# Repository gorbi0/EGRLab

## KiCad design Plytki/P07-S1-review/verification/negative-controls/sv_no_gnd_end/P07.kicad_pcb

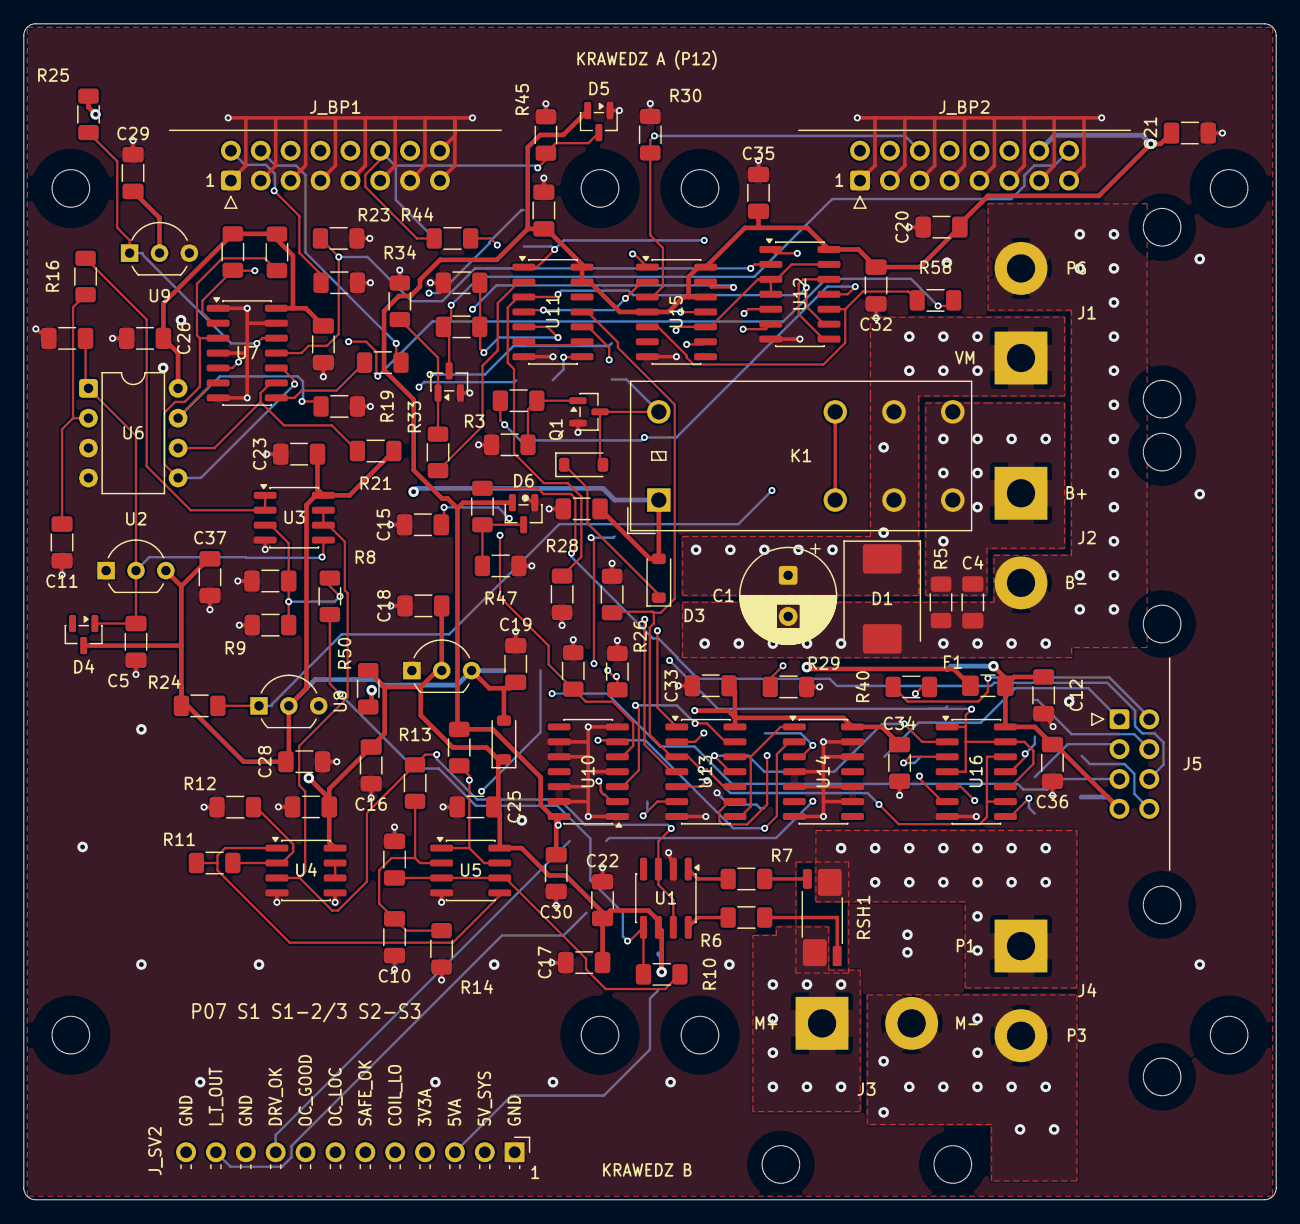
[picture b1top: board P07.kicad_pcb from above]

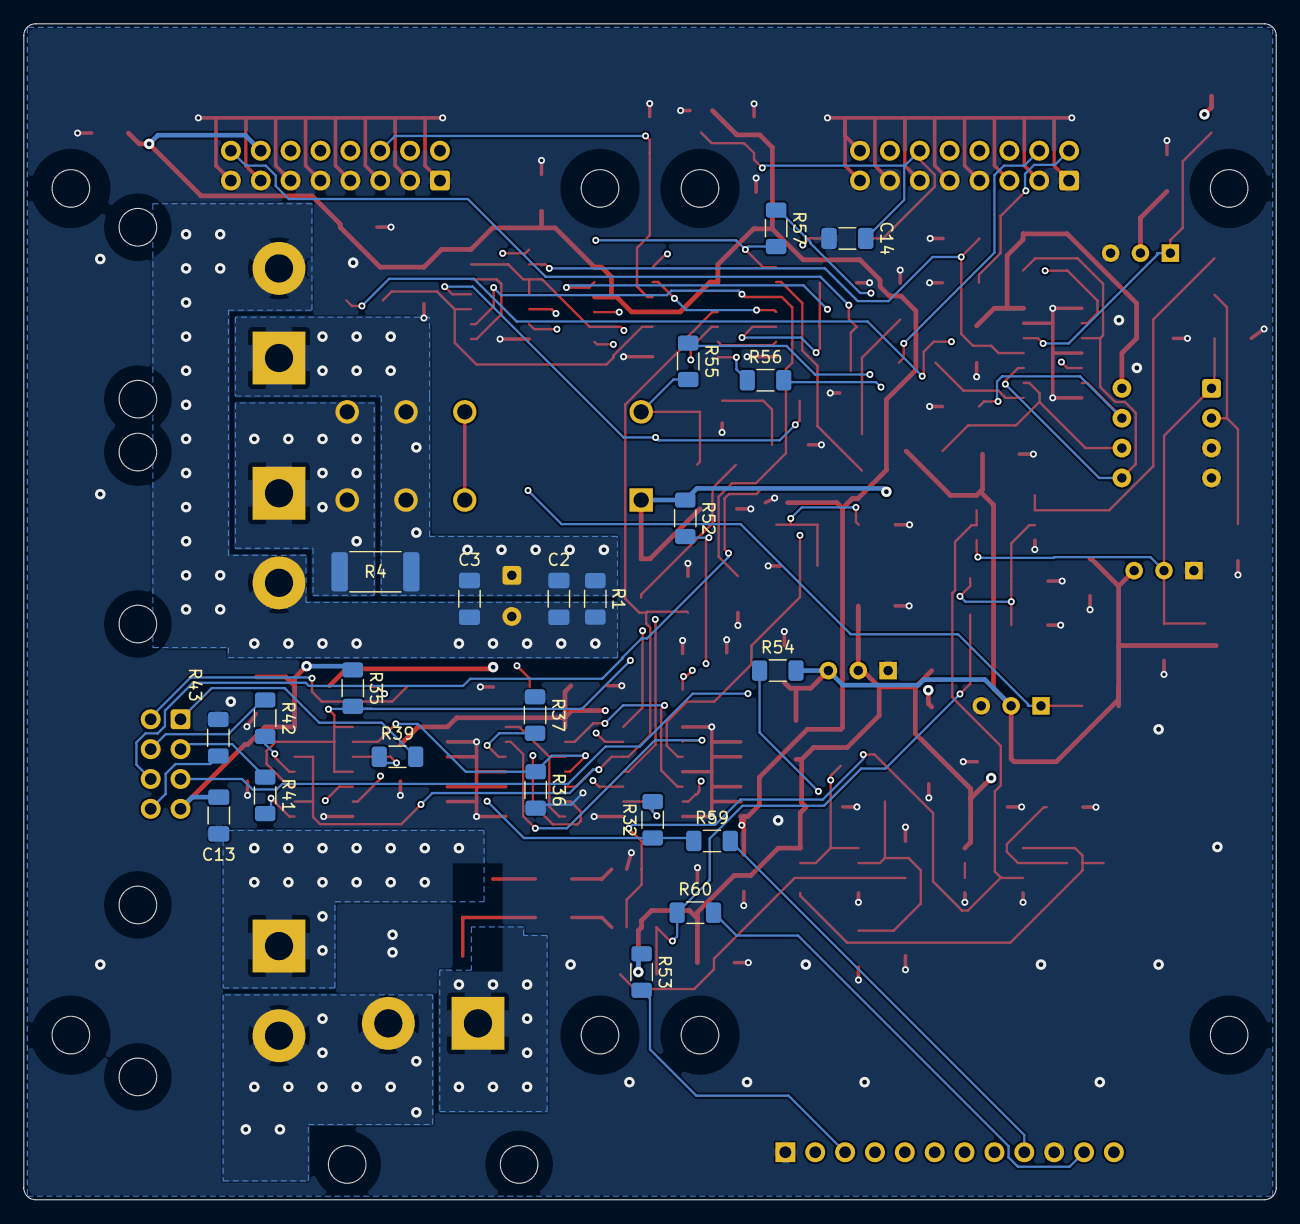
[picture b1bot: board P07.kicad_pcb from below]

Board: 4 copper layers, 106.5 x 100.0 mm, 140 parts (22 on the bottom side), 90 nets.

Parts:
C1: 220u; CP_Radial_D8.0mm_P3.50mm
C2, C18: 1u; C_1206_3216Metric_Pad1.33x1.80mm_HandSolder
C3, C4, C6, C7, C13, C14, C15, C17, C20, C22, C23, C24, C25, C26, C27, C28, C29, C30, C31, C32, C33, C34, C35, C36, C37: 100n; C_1206_3216Metric_Pad1.33x1.80mm_HandSolder
C5, C19: 4.7u; C_1206_3216Metric_Pad1.33x1.80mm_HandSolder
C8: 1n; C_1206_3216Metric_Pad1.33x1.80mm_HandSolder
C9, C12, C16, C21: 10u; C_1206_3216Metric_Pad1.33x1.80mm_HandSolder
C10: 10n; C_1206_3216Metric_Pad1.33x1.80mm_HandSolder
C11: 470p; C_1206_3216Metric_Pad1.33x1.80mm_HandSolder
D1: SMCJ18A; D_SMC
D2: 1N4148W; D_SOD-123
D3: BZT52C15; D_SOD-123
D4: BAT54; SOT-23
D5, D6: BAT54S; SOT-23
D7: B5819W; D_SOD-123
F1: PTC 0.12A; Fuse_1206_3216Metric_Pad1.42x1.75mm_HandSolder
H1, H2, H3, H4, H5, H6, H7, H8: M3 NPTH
J1: VMOTOR; PTH_VMOTOR
J2: MOD B+/B-; PTH_MODPWR
J3: MOD M+/M-; PTH_MODOUT
J4: TEST; PTH_TEST
J5: J_MOD; IDC-Header_2x04_P2.54mm_Horizontal
J_BP1: J_BP1; IDC-Header_2x08_P2.54mm_Horizontal
J_BP2: J_BP2; IDC-Header_2x08_P2.54mm_Horizontal
J_SV2: J_SV2 SERWIS 1x12; PinHeader_1x12_P2.54mm_Horizontal
K1: G2RL-1-E DC5; Relay_SPDT_Omron_G2RL-1-E
Q1: AO3400A; SOT-23
Q2: MMBT3904; SOT-23
R1, R5, R12, R14, R15, R18, R19, R23, R24, R25, R33, R60: 10K; R_1206_3216Metric_Pad1.30x1.75mm_HandSolder
R2, R32, R39, R40, R41, R42: 100R; R_1206_3216Metric_Pad1.30x1.75mm_HandSolder
R3, R17, R20, R26, R27, R28, R29, R30, R34, R35, R36, R37, R38, R45, R47: 100K; R_1206_3216Metric_Pad1.30x1.75mm_HandSolder
R4: 1K; R_2512_6332Metric_Pad1.40x3.35mm_HandSolder
R6, R7, R43, R50: 10R; R_1206_3216Metric_Pad1.30x1.75mm_HandSolder
R8, R9: 5.11K; R_1206_3216Metric_Pad1.30x1.75mm_HandSolder
R10, R31, R52, R53, R54, R55, R56, R57, R58, R59: 1K; R_1206_3216Metric_Pad1.30x1.75mm_HandSolder
R11: 8.06K; R_1206_3216Metric_Pad1.30x1.75mm_HandSolder
R13: 40.2K; R_1206_3216Metric_Pad1.30x1.75mm_HandSolder
R16, R22: 47R; R_1206_3216Metric_Pad1.30x1.75mm_HandSolder
R21: 47K; R_1206_3216Metric_Pad1.30x1.75mm_HandSolder
R44, R46: 4K7; R_1206_3216Metric_Pad1.30x1.75mm_HandSolder
R51: 1M; R_1206_3216Metric_Pad1.30x1.75mm_HandSolder
RSH1: 5m; R_Shunt_Vishay_WSK2512_T1.19mm_SenseE1.70
U1: INA240A2; SOIC-8_3.9x4.9mm_P1.27mm
U2: MCP1525-I/TO; TO-92_Inline_Wide
U3, U4: MCP6022-I/SN; SOIC-8_3.9x4.9mm_P1.27mm
U5: TLV1702AIDR; SOIC-8_3.9x4.9mm_P1.27mm
U6: MCP3201-BI/P; DIP-8_W7.62mm
U7, U10: 74LVC125AD; SOIC-14_3.9x8.7mm_P1.27mm
U8: MCP120-300DI/TO; TO-92_Inline_Wide
U9: MCP120-450DI/TO; TO-92_Inline_Wide
U11: 74LVC14AD; SOIC-14_3.9x8.7mm_P1.27mm
U12, U13, U14: SN74HC08D; SOIC-14_3.9x8.7mm_P1.27mm
U15: SN74HC74D; SOIC-14_3.9x8.7mm_P1.27mm
U16: 74AHCT125D; SOIC-14_3.9x8.7mm_P1.27mm
U18: MCP1702-3302E/TO; TO-92_Inline_Wide

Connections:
3V3A_P07: C19.1, C23.1, C26.1, C27.1, C28.1, C37.1, D4.3, D7.2, R17.1, R18.1, R21.1, R24.1, R54.1, U2.3, U3.8, U6.8, U7.14, U8.2, U18.3
3V3_IO: C20.1, C21.1, C30.1, C31.1, C32.1, C33.1, C34.1, C35.1, D5.2, D6.2, J_BP2.14, R15.2, U10.14, U11.13, U11.14, U12.14, U13.14, U14.14, U15.4, U15.12, U15.14
5VA_P07: C16.1, C17.1, C18.1, C22.1, C24.1, C25.1, C29.1, D7.1, R25.1, R50.2, R53.1, U1.6, U4.8, U5.8, U9.2, U18.2
5V_MOD: C12.1, C13.1, C36.1, F1.2, J5.7, R35.1, U16.14
5V_SYS: C9.1, D3.2, F1.1, J_BP2.10, J_BP2.12, K1.A1, R50.1, R52.1
/ANA/INA_MINUS: R7.2, U1.1
/ANA/INA_PLUS: R6.2, U1.8
/ANA/I_DIV: C7.1, R8.2, R9.1, U3.3
/ANA/I_FILT: C8.1, R10.2, U5.3, U5.6
/ANA/OC_FB: R11.2, R12.1, U4.2
/ANA/OC_HIGH: R11.1, U4.1, U5.5
/ANA/OC_LOW: C10.1, R13.2, R14.1, U5.2
/ANA/OC_UNUSED: U4.6, U4.7
/ANA/REF_BUF: R13.1, U1.3, U1.7, U3.6, U3.7, U4.3
/DIG/ADC_AIN: C11.1, R16.2, U6.2
/DIG/ADC_DOUT: R21.2, U6.6, U7.9
/DIG/CLK_LOCAL: R19.1, U6.7, U7.6
/DIG/CS_LOCAL_N: R18.2, U6.5, U7.3, U7.10
/DIG/DOUT_TX: R22.1, U7.8
/LOGIKA/DRIVE_OK_L: R32.1, U13.6
/LOGIKA/INA_P07: U10.3, U13.13
/LOGIKA/INB_P07: U10.6, U14.2
/LOGIKA/LOCAL_CLEAR_N: U12.6, U15.1
/LOGIKA/NO_TRIP: U13.5, U15.9
/LOGIKA/OC_B: Q2.1, R33.2, R34.1
/LOGIKA/OC_FAULT: R33.1, U11.2
/LOGIKA/PERMIT_ARMED: U12.8, U12.12
/LOGIKA/PERMIT_N: U11.4, U15.2
/LOGIKA/PWM_EN: U13.8, U13.12, U14.1
/LOGIKA/RAILS_OK: U12.3, U12.4, U12.13, U13.4, U15.10
/LOGIKA/SAFE_BAD: U11.6, U11.9
/LOGIKA/SAFE_SENSE: R31.2, R51.1, U11.5
/LOGIKA/SUP3_N: R24.2, U8.1, U12.1
/MOC/KPWR_B: Q1.1, R2.2, R3.1
/MOC/KPWR_CLAMP: D2.1, D3.1
/MOC/MOD_BP: C4.1, J2.1, K1.14, R4.2, R5.1
/MOC/MOD_MP: J3.1, RSH1.1
/MOC/T_EGR_P1: J4.1, RSH1.4
/MOC/T_EGR_P3: J3.2, J4.2
/MODUL/LEN_D: R42.1, U16.11
/MODUL/LPWM: J5.2, R40.2
/MODUL/LPWM_D: R40.1, U16.6
/MODUL/L_EN: J5.4, R42.2
/MODUL/L_IS: J5.6, R46.1
/MODUL/MOD_GND: J5.8, R43.2
/MODUL/REN_D: R41.1, U16.8
/MODUL/RPWM: J5.1, R39.2
/MODUL/RPWM_D: R39.1, U16.3
/MODUL/R_EN: J5.3, R41.2
/MODUL/R_IS: J5.5, R44.1
/SERWIS/SRV_3V3A_P07: J_SV2.4, R54.2
/SERWIS/SRV_5VA_P07: J_SV2.3, R53.2
/SERWIS/SRV_5V_SYS: J_SV2.2, R52.2
/SERWIS/SRV_DRIVE_OK: J_SV2.9, R59.2
/SERWIS/SRV_I_T_OUT: J_SV2.11, J_SV2.12, R60.2
/SERWIS/SRV_KPWR_COIL_LOW: J_SV2.5, R55.2
/SERWIS/SRV_OC_GOOD: J_SV2.8, R58.2
/SERWIS/SRV_OC_LOCAL_N: J_SV2.7, R57.2
/SERWIS/SRV_SAFE_OK: J_SV2.6, R56.2
ADC_BUF: R16.1, U3.1, U3.2
ADC_DOUTA: J_BP1.4, R22.2
ADC_SCLK: J_BP1.2, R20.1, U7.5
ARM_CLK: J_BP2.6, R30.1, U15.3, U15.11
CS_ITEST_N: J_BP1.6, R17.2, U7.2
DRIVE_EN: R38.1, U11.11, U13.3, U13.10, U16.9, U16.12
DRIVE_OK: J_BP2.8, R32.2, R59.1
DRV_OFF: R35.2, U11.10, U16.1, U16.4, U16.10, U16.13
ENA_DIAG: C14.1, D5.3, J_BP1.12, R44.2, R45.1
ENB_DIAG: C15.1, D6.3, J_BP1.14, R46.2, R47.1
GND: C5.2, C6.2, C7.2, C8.2, C9.2, C10.2, C11.2, C12.2, C13.2, C14.2, C15.2, C16.2, C17.2, C18.2, C19.2, C20.2, C21.2, C22.2, C23.2, C24.2, C25.2, C26.2, C27.2, C28.2, C29.2, C30.2, C31.2, C32.2, C33.2, C34.2, C35.2, C36.2, C37.2, D5.1, D6.1, J_BP1.1, J_BP1.3, J_BP1.5, J_BP1.7, J_BP1.9, J_BP1.11, J_BP1.13, J_BP1.15, J_BP1.16, J_BP2.1, J_BP2.3, J_BP2.5, J_BP2.7, J_BP2.9, J_BP2.11, J_BP2.13, J_BP2.15, J_SV2.1, J_SV2.10, Q1.2, Q2.2, R3.2, R9.2, R12.2, R14.2, R19.2, R20.2, R23.2, R26.2, R27.2, R28.2, R29.2, R30.2, R34.2, R36.2, R37.2, R38.2, R43.1, R45.2, R47.2, R51.2, U1.2, U2.1, U3.4, U4.4, U4.5, U5.4, U6.3, U6.4, U7.1, U7.4, U7.7, U7.13, U8.3, U9.3, U10.1, U10.4, U10.7, U10.9, U10.10, U10.12, U10.13, U11.7, U12.7, U13.7, U14.4, U14.5, U14.7, U14.9, U14.10, U14.12, U14.13, U15.7, U16.7, U18.1
I_T_OUT: R8.1, R10.1, R60.1, U1.5
KPWR_COIL_LOW: D2.2, K1.A2, Q1.3, R55.1
K_MINUS: R7.1, RSH1.3
K_PLUS: R6.1, RSH1.2
LOCAL_PERMIT: R2.1, U12.11, U13.1
LPWM_L: R37.1, U14.3, U16.5
MOTOR_INA: J_BP1.8, R26.1, U10.2
MOTOR_INB: J_BP1.10, R27.1, U10.5
MOTOR_PERMIT: J_BP2.2, R28.1, U11.3, U12.9
OC_GOOD: R58.1, U12.10, U15.5
OC_LOCAL_N: R15.1, R57.1, U5.1, U5.7, U11.1, U12.5, U15.13
PGND: C1.2, C2.2, C3.2, C4.2, D1.2, J1.2, J2.2, R1.2, R5.2
PWM_OUT: J_BP2.4, R29.1, U13.9
REF25: C5.1, C6.1, D4.1, U2.2, U3.5, U6.1
RPWM_L: R36.1, U13.11, U16.2
SAFE_N: J_BP2.16, Q2.3, R31.1
SAFE_OK: R56.1, U11.8, U13.2
SUP5_N: R23.1, U7.11, U12.2
SUP5_RAW: R25.2, U7.12, U9.1
VMOTOR: C1.1, C2.1, C3.1, D1.1, J1.1, K1.11, R1.1, R4.1
